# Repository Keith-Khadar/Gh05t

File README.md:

# Project Overview

This project aims to design and develop a wearable EEG headset with an integrated data acquisition system. Using OpenBCI Ultracortex Mark IV as a template, the headset is designed to map the electrodes according to the 10-20 system. We expand on this design by integrating our own 3D printed or button-snap electrodes for enhanced modularity. Additionally, we investigate various EEG data acquistion hardware options, varying in cost, precision, and usability, to enhance accessibility and modularity in EEG systems - ranging from off-the-shelf hardware to custom-designed PCBs and circuit designs. The hardware will communicate with a computer for analysis by a machine learning (ML) model to detect gestures or possible speech, with the possibility of integration into Virtual-Reality (VR) applications. Lastly, the system will feature a custom GUI, enabling users to visualize EEG data in real-time from the various custom hardware configurations we explore.

We provide various levels to users depending on cost, precision, and usability:

| Feature                     | High Performance Development Board[^1]    | Balanced Performance Board[^2]                | Low Cost EEG Filtering Circuit[^3]            |
| --------------------------- | ----------------------------------------- | --------------------------------------------- | --------------------------------------------- |
| **Number of Channels**      | 8\*                                       | 8\*                                           | 8                                             |
| **Resolution**              | 24-bit                                    | 24-bit                                        | 12-bit                                        |
| **Typical Sampling Rate**   | 250 Hz                                    | 250 Hz                                        | <33 Hz                                        |
| **ADC Chip**                | ADS1299-IPAG                              | ADS1299-IPAG                                  | Internal RPi Pico ADC                         |
| **Board**                   | EEG Development Board with ESP32-S3       | Custom PCB                                    | Custom breadboard/featherboard circuit        |
| **Microcontroller**         | XIAO ESP32-C6                             | DFRobot Firebeetle ESP32 32D                  | Raspberry Pi Pico W                           |
| **Connectivity**            | USB-C/Bluetooth/WiFi                      | Micro-USB/Bluetooth/WiFi                      | Micro-USB/WiFi                                |
| **Power Source**            | Battery/USB                               | Battery/USB                                   | Battery/USB                                   |
| **Battery Life**            | 8 hours                                   | -                                             | <1 hour                                       |
| **GUI Support**             | OpenBCI GUI                               | Custom GUI                                    | Custom GUI                                    |
| **Form Factor**             | Button Snap Electrodes w/ OpenBCI Headset | 3D printed Claw Electrodes w/ OpenBCI Headset | 3D printed Claw Electrodes w/ Custom Headband |
| **Communication Protocols** | SPI, ESPNOW, UART                         | SPI, BLE                                      | UDP WebSocket                                 |
| **Price**                   | ~$375                                     | ~$100                                         | ~$50                                          |

\* The ADS1299 has the capabilities to daisy chain, therefore expanding the channel number from 8 to 16 but it is not fully implemented on the custom PCB. Refer to the ADS1299 PCB folder for additional information.

[^1]: Refer to [High_Performance\README.md](https://github.com/Keith-Khadar/Gh05t/tree/main/High_Performance) for more information on the setup and specifics for the system.
[^2]: Refer to [Balanced_Performance\README.md](https://github.com/Keith-Khadar/Gh05t/tree/main/Balanced_Performance) for more information on the setup and specifics for the system.
[^3]: Refer to [Low_Cost\README.md](https://github.com/Keith-Khadar/Gh05t/tree/main/Low_Cost) for more information on the setup and specifics for the system.

## Completed Work/In Progress for Milestone Production Release

-   **Working Balanced Performance Pipeline (ADS1299 Breakout PCB)**: Eye blinks were detected successfully in the FFT and Time Series plots but was unable to receive consistent and robust results after each trial.
    -   Work in progress of doing trial and error to reproduce results.
-   **Housing Design for Balanced Performance Board (Breakout PCB)**: A CAD design of a housing unit for the ADS1299 Breakout PCB was completed.
-   **Receiver code optimization for the High Performance board**: The receiver code was optimized for better efficiency on the high-performance board by restructuring logic, minimizing redundant operations, and improving resource utilization.
-   **Optimizing Real Time Reading on the GUI**: Since eye blinks were successfully shown in the time series, the SDED, with the calibration of the delta and alpha variables, was able to successfully label with minimal latency the sample positions where the blinking occurred.
-   **EEG Game Application**: In order to expand the application of using the EEG data and detecting events like eye blinking, a VR and simple blinking game was created. A WebSocket host was created in the GUI and successfully broadcasts the SDED labels to any client to act as a controller for a game.
-   **Signal Preprocessing** : The EEG signal preprocessing pipeline is fully implemented, ensuring artifact removal, filtering, and independent component extraction before further processing. FastICA, InfoMax, NLMS and VSS-APA are implemented to extract information components from raw EEG signals in real-time.
-   **Event Detection/Prediction Model**: The EEG-based event detection pipeline and machine learning models have been developed to analyze real-time brain activity and infer motor function. NLMS, Batch-Wiener Filter and VSS-APA have been implemeted for predictions - Statistical Deviation Event Detection Model and Information Theoretic Learning Point Process Detection Models have been implemented for more sophisticed event flagging.

# Project Architecture

### <p align="center">**High Performance Development Board**[^1]</p>

| <div style="width:400px">Hardware Architecture & Wiring</div>  | Components  | Communication Protocols  |
| ----------------------- | ----------------------- | ----------------------- |
|  | - OpenBCI 3D Headset Design<br> - Depth-adjustable spring loaded 3D printed assembly with metal snap electrodes provides good signal strength for EEG signals <br> - EEG ESP Development Board with ESP32-S3 <br> - XIAO ESP32-C6<br> - Protective case for the development board<br> | - SPI communication between ADS1299 chip and ESP32-S3<br> - ESP-NOW WiFi data transmission between Development Board and ESP32-C6<br> - UART serialized data transmission through USB-C connection between ESP32-C6 and computer receiver <br> |

-   **Software**
    -   Once the ESP32-C6 captures the incoming EEG data from the ESP32-S3, the UART data is captured through a python script and written to a file. The captured EEG data in this file can be viewed using OpenBCI GUI. The EEG data in this file will be feed to the machine learning model to draw inferences after analysis of the data.
    -   A python script is employed to label and timestamp the 8-channel EEG blinking data. This script facilitates the real-time processing and organization of the data, ensuring that each blink event is accurately marked with its corresponding timestamp for subsequent analysis.
    -   An end-to-end high-performance EEG pipeline leverages an ESP32 EEG board and ESP32-C6 to wirelessly transmit 8-channel, ultra-low-noise data at 250 samples/sec via ESP-NOW, enabling real-time processing in Python and visualization through OpenBCI GUI or a custom interface.

### <p align="center">**Balanced Performance Board**[^2]</p>

| <div style="width:450px">Hardware Architecture & Wiring</div>  | Components  | Communication |
| ----------------------- | ----------------------- | ----------------------- |
|    | - OpenBCI 3D Headset Design<br> - 3D Printed Claw Electrodes<br> - Custom ADS1299 PCB<br> - DFRobot Firebeetle ESP32 32D <br> | - SPI communication between the ADS1299 PCB and Firebeetle ESP32 <br> - BLE data transmission between the Firebeetle ESP32 and computer receiver <br> |

-   **Software**
    -   Once the Firebeetle ESP32 is supplied power, the BLE server is turned on and ready to transmit data to any device that connects to the server. The **GH05T GUI** is used to connect to the BLE server and read incoming real-time data.

### <p align="center">**Low Cost Filtering Circuit**[^3]</p>

| <div style="width:500px">Hardware Architecture & Wiring</div>   | Components | Communication Protocols |
| ----------------------- | ----------------------- | ----------------------- |
|  | - Custom Filtering and Component Circuit on breadboard/featherboard <br> - Raspberry Pi Pico W <br> | - TCP WebSocket data transmission between Raspberry Pi Pico W and computer receiver |

-   **Software**
    -   Once the Raspberry Pi Pico W is supplied power,UDP WebSocket is opened and transmits data to any device that connects to the server. The **GH05T GUI** is used to connect to the WebSocket server and read incoming real-time data.

### <p align="center">**GH05T Graphic User Interface**[^4]</p>

| <div style="width:300px">Function and Feature Architecture</div> | Visuals/GUI  |
| ----------------| ---------------------- |
|  |  [PyQt](https://doc.qt.io/qtforpython-6/) & [Matplotlib](https://matplotlib.org/): Widget and EEG Data Visualization |

[^4]: Refer to [Gh05t GUI\README.md](https://github.com/Keith-Khadar/Gh05t/tree/main/Gh05t%20GUI) for more information on the setup and specifics on the GUI.

### <p align="center">**Signal Processing and Machine Learning**[^5]</p>

-   **EEG Signal Pre-processing**:

    -   Format:
        -   Input: Raw 4 channel electrode data
        -   Output: K-Independent Signals (Components)
    -   Processing Options:
        -   FastICA , NLMS: Fast Inference
        -   InfoMax or VSS-APA: Versatility & Robustness

-   **EEG Signal Machine Learning**:
    -   Format:
        -   Input: K-Independent Signals (Components)
        -   Output: User Defined Target Output
    -   Target:
        -   User Defined Target Desired Output, i.e. eye activity or motion.
    -   Model:
        -   Structure: Artifical Neural Network (Regressor)
        -   Pre-Training: PCA-Pretraining for optimal features
        -   Training: Network Tuning based on Target Data

[^5]: Refer to [Machine_Learning\README.md](https://github.com/Keith-Khadar/Gh05t/tree/main/Machine_Learning) for more information on the setup and specifics.

## Known Bugs

- The Balanced Performance Board ADS1299 completely stopped working after trying to fit the casing to the hardware. This was an unexpected issue that is not able to be understood. Possible issues that could have occurred for the chip to completely stop working is somehow the chip received a surge of power that could have damaged it. 

## Difficulties/Challenges

-   **3D Printing Fail**: Weak legs on 3D electrodes
    -   The initial model found and used for the electrodes has spindly legs. In combination with two snaps of the filament during printing, the legs were incredibly weak and many snapped during removal from the print bed.
    -   Fix: Load filament onto spool to eliminate snapping during print. Custom design electrodes with filleted legs to enhance their strength. Increase the number of walls when slicing model for printing.
    -   Above fix solved combined with printing on a higher quality printer and in a different orientation fixed the issues.
-   **Snap Plating**: Purchased snaps are covered in non-conductive coating
    -   Prevented soldering, but can be scrapped off with a knife.
    -   Reduces signal integritty of electrodes.
    -   Fix: Looking into alternative unplated snap connectors.
    -   Above fix solves the issue in initial testing. Will continue to monitor as further testing is conducted.
-   **Inaccurate EEG Data**: Data recorded during initial testing is inaccurate.
    -   The poor quality electrodes(see snap plating challenge & 3d printing fail) as well as the ADC optimized for Electromyography (EMG) data recording instead of the use case of Electroencephalography (EEG), resulted in poor quality data.
    -   Fix: Custom designed PCB breakout board for the ADS1299 which is designed for EEG data acquisition.
-   **GUI Real Time Data**: Optimizing the timing between data conversion from the ADS1299 to the GUI has introduced latency.
    -   Fix: Utilizing threading and precise timing between frame updating and loading.
-   **ADS1299 Electrode Setup**: Setting up the registers for specific BIAS, SRB1/2, and Electrode connections proved difficult with our system. This was causing reading alpha waves to be difficult.
    -   Fix: Using the SRB1, connected to the earlobe/mastoid, routed to all the negative parts of the electrode channels for reference. Using the BIAS, also connected to the earlobe/mastoid, routed to the postive electrode channels for signal derivation.

## License

## Contact

## Acknowledgements

We would like to extend our gratitude to OpenBCI for having open source repositories with headset designs, ADS1299 libraries, and user interface code. These repositories played a significant role in the success of the project!

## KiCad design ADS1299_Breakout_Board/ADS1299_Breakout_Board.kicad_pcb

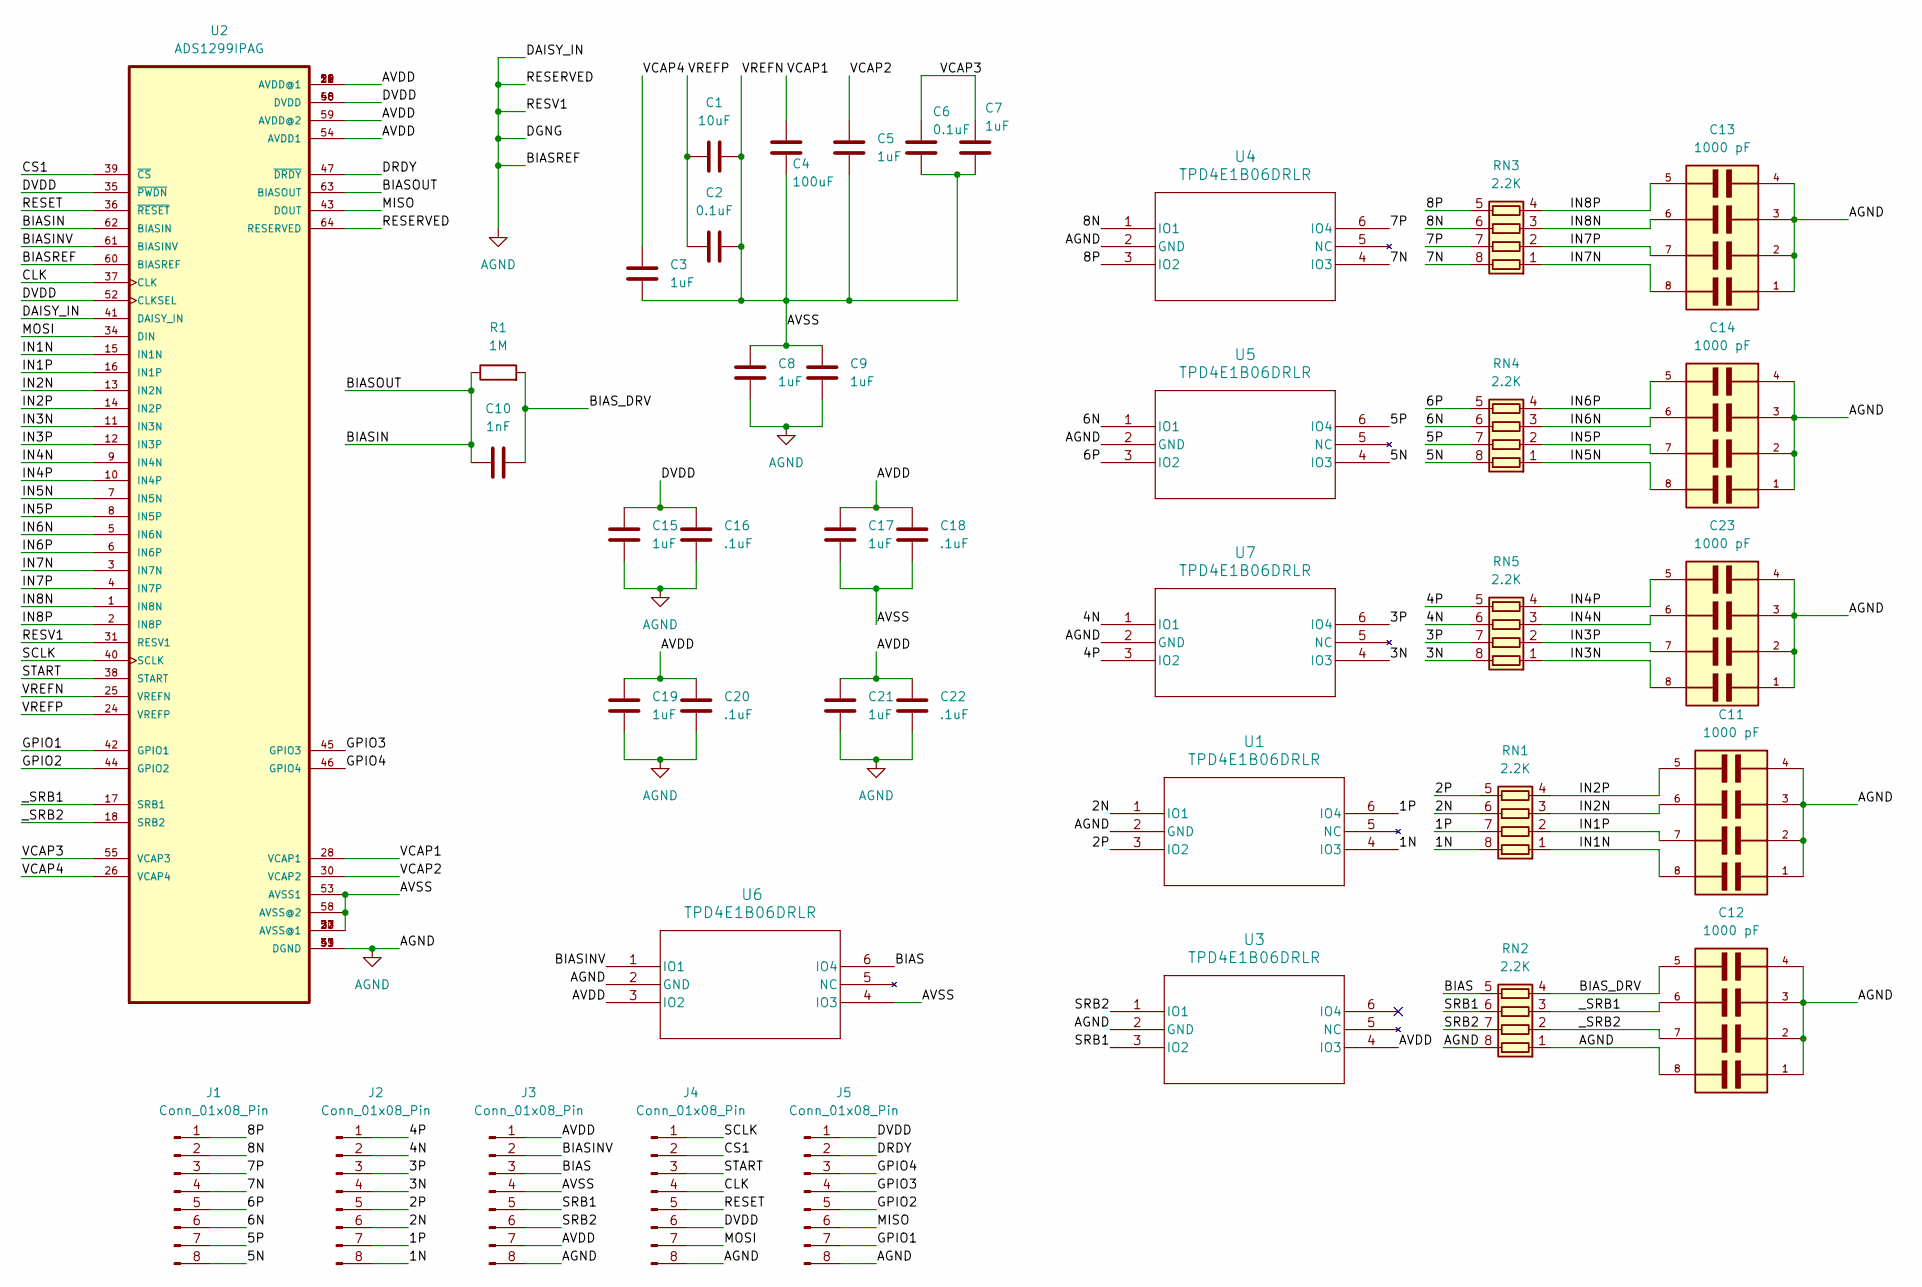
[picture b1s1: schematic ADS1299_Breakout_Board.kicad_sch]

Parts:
C1: 10uF; C_0805_2012Metric
C2, C6: 0.1uF; C_0805_2012Metric
C3, C5, C7, C8, C9, C15, C17, C19, C21: 1uF; C_0805_2012Metric
C4: 100uF; C_0805_2012Metric
C10: 1nF; C_0805_2012Metric
C11, C12, C13, C14, C23: 1000 pF; CAPCAF50P200X125X85-8; PARTREV Dec 2014
C16, C18, C20, C22: .1uF; C_0805_2012Metric
J1, J2, J3, J4, J5: Conn_01x08_Pin; PinHeader_1x08_P2.54mm_Vertical
R1: 1M; R_0805_2012Metric
RN1, RN2, RN3, RN4, RN5: 2.2K; R_Array_Concave_4x0603
U1, U3, U4, U5, U6, U7: TPD4E1B06DRLR; DRL6_TEX
U2: ADS1299IPAG; QFP50P1200X1200X120-64N

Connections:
/1N: J2.8, RN1.8 (R1.2), U1.4 (IO3)
/1P: J2.7, RN1.7 (R2.2), U1.6 (IO4)
/2N: J2.6, RN1.6 (R3.2), U1.1 (IO1)
/2P: J2.5, RN1.5 (R4.2), U1.3 (IO2)
/3N: J2.4, RN5.8 (R1.2), U7.4 (IO3)
/3P: J2.3, RN5.7 (R2.2), U7.6 (IO4)
/4N: J2.2, RN5.6 (R3.2), U7.1 (IO1)
/4P: J2.1, RN5.5 (R4.2), U7.3 (IO2)
/5N: J1.8, RN4.8 (R1.2), U5.4 (IO3)
/5P: J1.7, RN4.7 (R2.2), U5.6 (IO4)
/6N: J1.6, RN4.6 (R3.2), U5.1 (IO1)
/6P: J1.5, RN4.5 (R4.2), U5.3 (IO2)
/7N: J1.4, RN3.8 (R1.2), U4.4 (IO3)
/7P: J1.3, RN3.7 (R2.2), U4.6 (IO4)
/8N: J1.2, RN3.6 (R3.2), U4.1 (IO1)
/8P: J1.1, RN3.5 (R4.2), U4.3 (IO2)
/AVDD: C17.1, C18.1, C19.1, C20.1, C21.1, C22.1, J3.1, J3.7, U2.19 (AVDD@1), U2.21 (AVDD@1), U2.22 (AVDD@1), U2.54 (AVDD1), U2.56 (AVDD@1), U2.59 (AVDD@2), U3.4 (IO3), U6.3 (IO2)
/AVSS: C1.2, C2.2, C3.2, C4.2, C5.2, C6.1, C7.2, C8.1, C9.1, C17.2, C18.2, J3.4, U2.20 (AVSS@1), U2.23 (AVSS@1), U2.25 (VREFN), U2.32 (AVSS@1), U2.53 (AVSS1), U2.57 (AVSS@1), U2.58 (AVSS@2), U6.4 (IO3)
/BIAS: J3.3, RN2.5 (R4.2), U6.6 (IO4)
/BIASIN: C10.2, R1.1, U2.62 (BIASIN), U2.63 (BIASOUT)
/BIASINV: J3.2, U2.61 (BIASINV), U6.1 (IO1)
/BIAS_DRV: C10.1, C12.5, R1.2, RN2.4 (R4.1)
/CLK: J4.4, U2.37 (CLK)
/CS1: J4.2, U2.39 (~CS)
/DRDY: J5.2, U2.47 (~DRDY)
/DVDD: C15.1, C16.1, J4.6, J5.1, U2.35 (~PWDN), U2.48 (DVDD), U2.50 (DVDD), U2.52 (CLKSEL)
/GPIO1: J5.7, U2.42 (GPIO1)
/GPIO2: J5.5, U2.44 (GPIO2)
/GPIO3: J5.4, U2.45 (GPIO3)
/GPIO4: J5.3, U2.46 (GPIO4)
/IN1N: C11.8, RN1.1 (R1.1), U2.15 (IN1N)
/IN1P: C11.7, RN1.2 (R2.1), U2.16 (IN1P)
/IN2N: C11.6, RN1.3 (R3.1), U2.13 (IN2N)
/IN2P: C11.5, RN1.4 (R4.1), U2.14 (IN2P)
/IN3N: C23.8, RN5.1 (R1.1), U2.11 (IN3N)
/IN3P: C23.7, RN5.2 (R2.1), U2.12 (IN3P)
/IN4N: C23.6, RN5.3 (R3.1), U2.9 (IN4N)
/IN4P: C23.5, RN5.4 (R4.1), U2.10 (IN4P)
/IN5N: C14.8, RN4.1 (R1.1), U2.7 (IN5N)
/IN5P: C14.7, RN4.2 (R2.1), U2.8 (IN5P)
/IN6N: C14.6, RN4.3 (R3.1), U2.5 (IN6N)
/IN6P: C14.5, RN4.4 (R4.1), U2.6 (IN6P)
/IN7N: C13.8, RN3.1 (R1.1), U2.3 (IN7N)
/IN7P: C13.7, RN3.2 (R2.1), U2.4 (IN7P)
/IN8N: C13.6, RN3.3 (R3.1), U2.1 (IN8N)
/IN8P: C13.5, RN3.4 (R4.1), U2.2 (IN8P)
/MISO: J5.6, U2.43 (DOUT)
/MOSI: J4.7, U2.34 (DIN)
/RESET: J4.5, U2.36 (~RESET)
/SCLK: J4.1, U2.40 (SCLK)
/SRB1: J3.5, RN2.6 (R3.2), U3.3 (IO2)
/SRB2: J3.6, RN2.7 (R2.2), U3.1 (IO1)
/START: J4.3, U2.38 (START)
/VCAP1: C4.1, U2.28 (VCAP1)
/VCAP2: C5.1, U2.30 (VCAP2)
/VCAP3: C6.2, C7.1, U2.55 (VCAP3)
/VCAP4: C3.1, U2.26 (VCAP4)
/VREFP: C1.1, C2.1, U2.24 (VREFP)
/_SRB1: C12.6, RN2.3 (R3.1), U2.17 (SRB1)
/_SRB2: C12.7, RN2.2 (R2.1), U2.18 (SRB2)
AGND: C8.2, C9.2, C11.1, C11.2, C11.3, C11.4, C12.1, C12.2, C12.3, C12.4, C12.8, C13.1, C13.2, C13.3, C13.4, C14.1, C14.2, C14.3, C14.4, C15.2, C16.2, C19.2, C20.2, C21.2, C22.2, C23.1, C23.2, C23.3, C23.4, J3.8, J4.8, J5.8, RN2.1 (R1.1), RN2.8 (R1.2), U1.2 (GND), U2.31 (RESV1), U2.33 (DGND), U2.41 (DAISY_IN), U2.49 (DGND), U2.51 (DGND), U2.60 (BIASREF), U2.64 (RESERVED), U3.2 (GND), U4.2 (GND), U5.2 (GND), U6.2 (GND), U7.2 (GND)

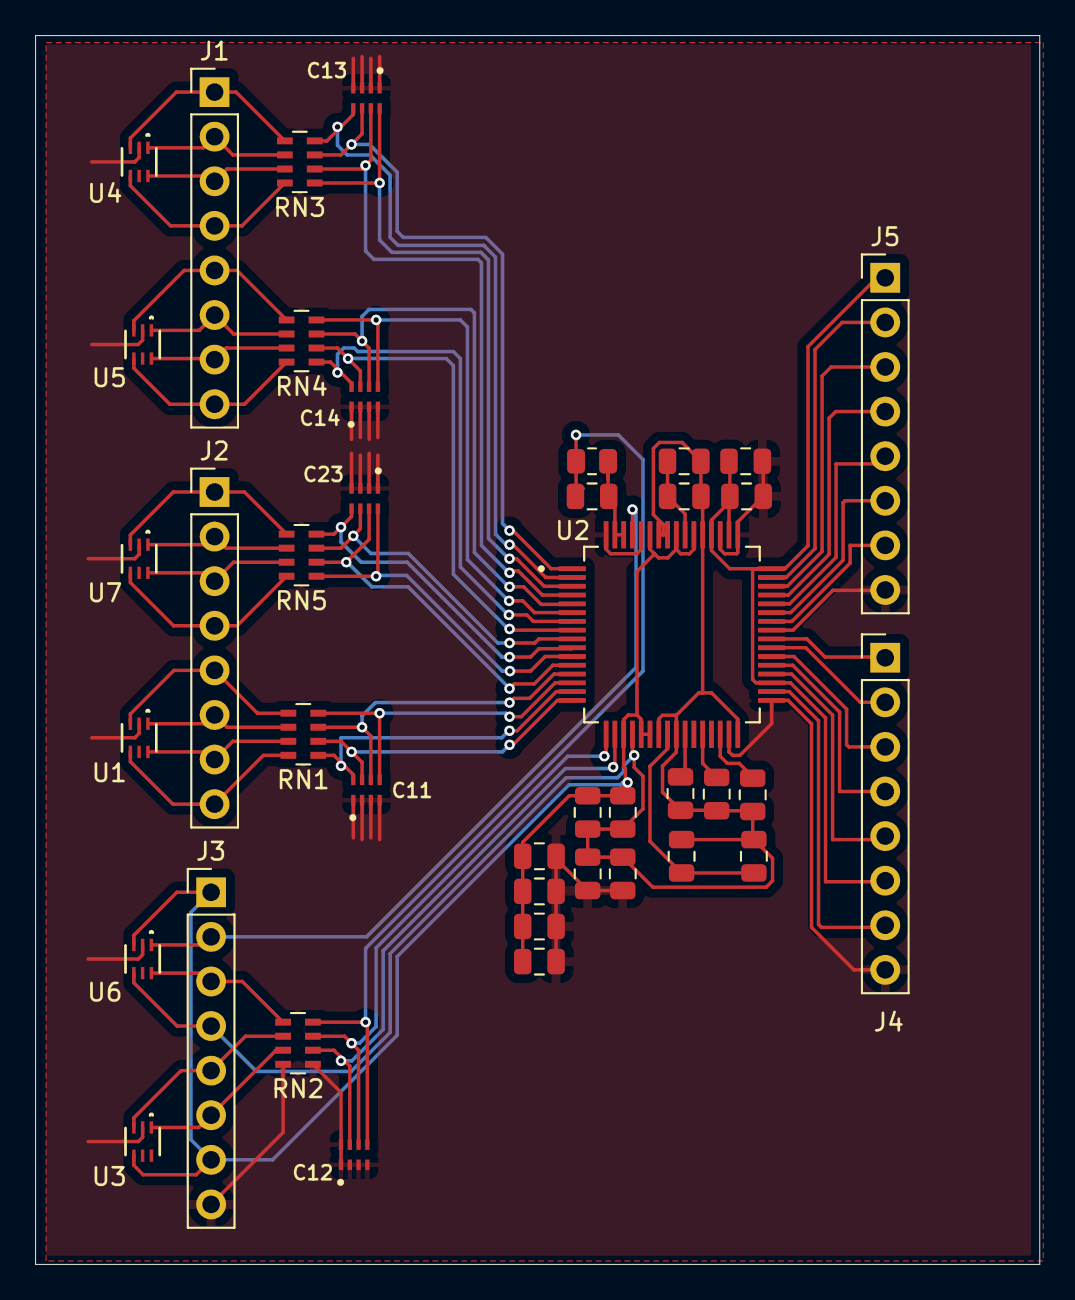
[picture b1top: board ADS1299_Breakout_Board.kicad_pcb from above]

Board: 2 copper layers, 57.2 x 70.0 mm, 41 parts (0 on the bottom side), 61 nets.

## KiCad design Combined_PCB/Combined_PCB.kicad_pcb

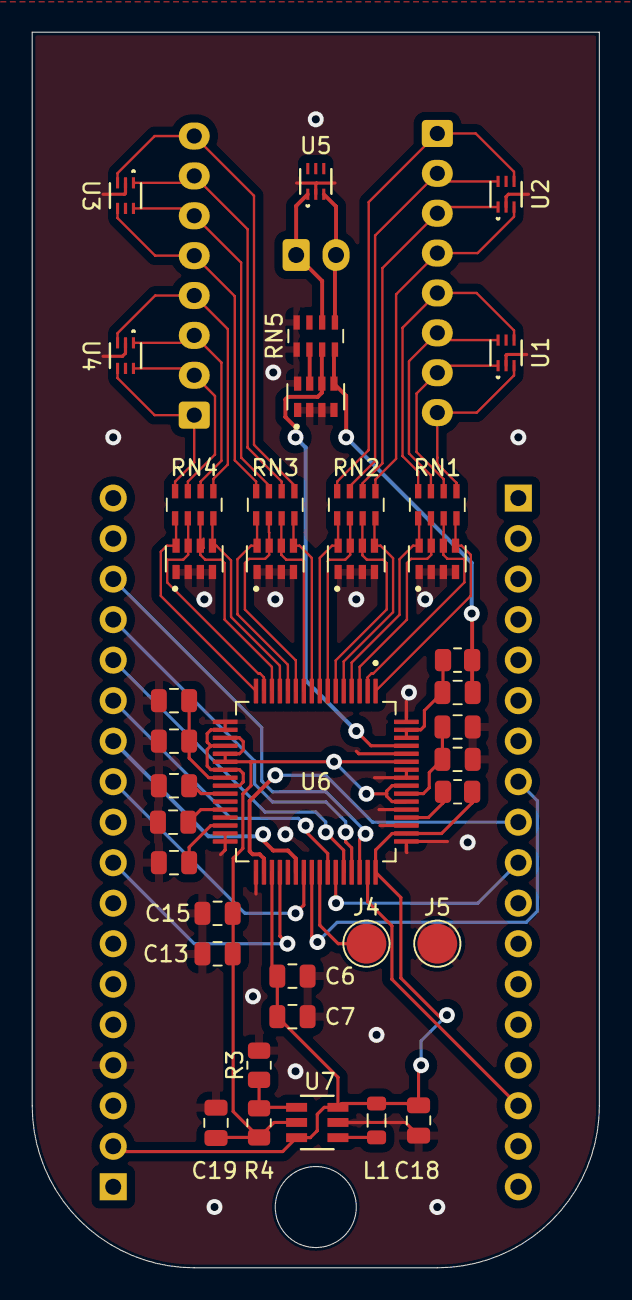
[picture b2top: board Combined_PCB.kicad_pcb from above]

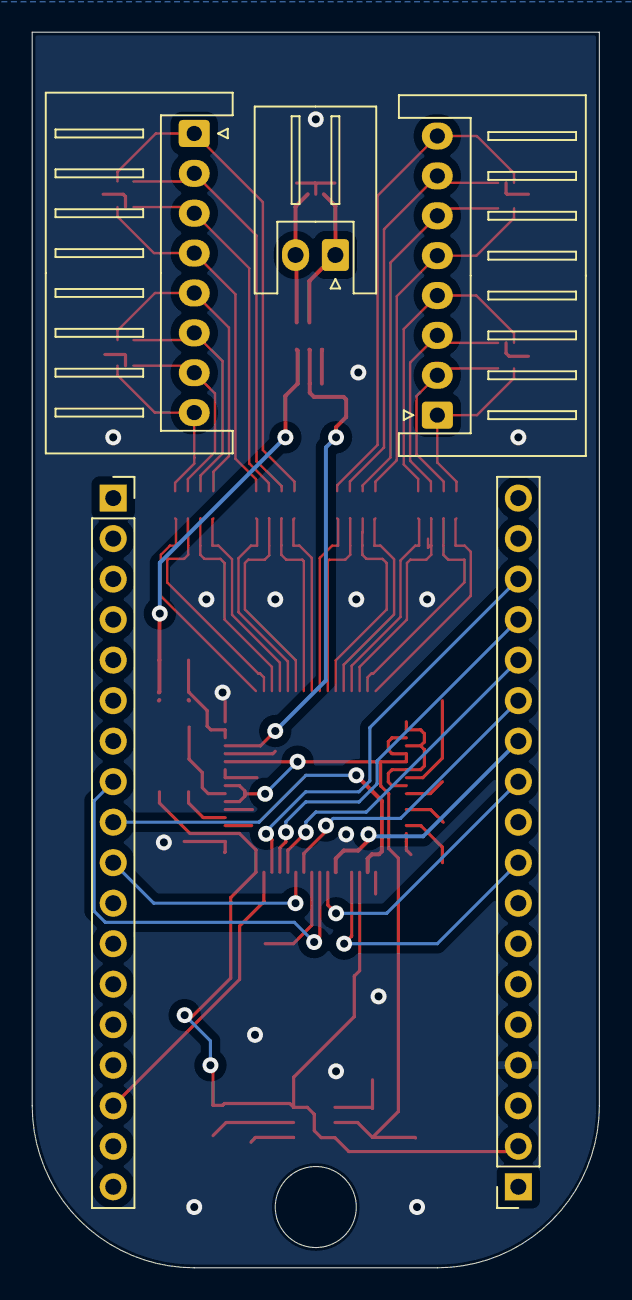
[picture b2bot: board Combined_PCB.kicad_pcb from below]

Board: 4 copper layers, 35.6 x 77.5 mm, 43 parts (5 on the bottom side), 61 nets.

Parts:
C1, C2, C3, C4, C5: 1000 pF; CAPCAV_W3A45C102KAT2A-8
C6, C12, C13, C16, C17: 1uF; C_0805_2012Metric
C7, C15: .1uF; C_0805_2012Metric
C8, C18, C19: 10uF; C_0805_2012Metric
C9, C14: 0.1uF; C_0805_2012Metric
C10: 100uF; C_0805_2012Metric
C11: 1nF; C_0805_2012Metric
J1, J3: Conn_01x08_Pin; JST_XH_S8B-XH-A_1x08_P2.50mm_Horizontal
J2: Conn_01x02_Pin; JST_XH_S2B-XH-A_1x02_P2.50mm_Horizontal
J4, J5: Conn_01x01_Pin; TestPoint_Pad_D2.5mm
J6, J7: Conn_01x18_Pin; PinSocket_1x18_P2.54mm_Vertical
L1: 4.7uH; L_0805_2012Metric
R1, R2: 1M; R_0805_2012Metric
R3: 309; R_0805_2012Metric
R4: 976; R_0805_2012Metric
RN1, RN2, RN3, RN4, RN5: 2.2K; R_Array_Concave_4x0603
U1, U2, U3, U4, U5: TPD4E1B06DRLR; DRL6_TEX
U6: ADS1299IPAG; QFP50P1200X1200X120-64N
U7: MCP1640BT-I/CHY; SOT-23-6_MC_MCH

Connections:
/ADS1299 & Microcontroller/3v3: C6.1, C7.1, C18.2, J6.2, L1.2, R2.2, U6.35 (~PWDN), U6.48 (DVDD), U6.50 (DVDD), U7.3 (EN), U7.6 (VIN)
/ADS1299 & Microcontroller/5v: C13.1, C15.1, C19.1, R4.2, U6.19 (AVDD@1), U6.21 (AVDD@1), U6.22 (AVDD@1), U6.54 (AVDD1), U6.56 (AVDD@1), U6.59 (AVDD@2), U7.5 (VOUT)
/ADS1299 & Microcontroller/BIASOUT: C11.2, R1.1, U6.62 (BIASIN), U6.63 (BIASOUT)
/ADS1299 & Microcontroller/CLK_SEL: R2.1, U6.52 (CLKSEL)
/ADS1299 & Microcontroller/CS: J6.11, U6.39 (~CS)
/ADS1299 & Microcontroller/DRDY: J7.16, U6.47 (~DRDY)
/ADS1299 & Microcontroller/GPIO1: J6.13, U6.42 (GPIO1)
/ADS1299 & Microcontroller/GPIO2: J6.14, U6.44 (GPIO2)
/ADS1299 & Microcontroller/GPIO3: J6.15, U6.45 (GPIO3)
/ADS1299 & Microcontroller/GPIO4: J6.16, U6.46 (GPIO4)
/ADS1299 & Microcontroller/MISO: J7.10, U6.43 (DOUT)
/ADS1299 & Microcontroller/MOSI: J7.9, U6.34 (DIN)
/ADS1299 & Microcontroller/RESET: J6.9, U6.36 (~RESET)
/ADS1299 & Microcontroller/SCLK: J7.8, U6.40 (SCLK)
/ADS1299 & Microcontroller/START: J6.12, U6.38 (START)
/ADS1299 & Microcontroller/VCAP1: C10.1, U6.28 (VCAP1)
/ADS1299 & Microcontroller/VCAP2: C12.1, U6.30 (VCAP2)
/ADS1299 & Microcontroller/VCAP3: C14.2, C16.1, U6.55 (VCAP3)
/ADS1299 & Microcontroller/VCAP4: C17.1, U6.26 (VCAP4)
/ADS1299 & Microcontroller/VREFP: C8.1, C9.1, U6.24 (VREFP)
/Inputs & Filtering/1N: J3.2, RN4.7 (R2.2), U4.6 (IO4)
/Inputs & Filtering/1P: J3.1, RN4.8 (R1.2), U4.4 (IO3)
/Inputs & Filtering/2N: J3.4, RN4.5 (R4.2), U4.3 (IO2)
/Inputs & Filtering/2P: J3.3, RN4.6 (R3.2), U4.1 (IO1)
/Inputs & Filtering/3N: J3.6, RN3.7 (R2.2), U3.6 (IO4)
/Inputs & Filtering/3P: J3.5, RN3.8 (R1.2), U3.4 (IO3)
/Inputs & Filtering/4N: J3.8, RN3.5 (R4.2), U3.3 (IO2)
/Inputs & Filtering/4P: J3.7, RN3.6 (R3.2), U3.1 (IO1)
/Inputs & Filtering/5N: J1.2, RN2.7 (R2.2), U2.6 (IO4)
/Inputs & Filtering/5P: J1.1, RN2.8 (R1.2), U2.4 (IO3)
/Inputs & Filtering/6N: J1.4, RN2.5 (R4.2), U2.3 (IO2)
/Inputs & Filtering/6P: J1.3, RN2.6 (R3.2), U2.1 (IO1)
/Inputs & Filtering/7N: J1.6, RN1.7 (R2.2), U1.6 (IO4)
/Inputs & Filtering/7P: J1.5, RN1.8 (R1.2), U1.4 (IO3)
/Inputs & Filtering/8N: J1.8, RN1.5 (R4.2), U1.3 (IO2)
/Inputs & Filtering/8P: J1.7, RN1.6 (R3.2), U1.1 (IO1)
/Inputs & Filtering/BIAS: J2.2, RN5.5 (R4.2), U5.3 (IO2)
/Inputs & Filtering/BIASINV: J2.1, RN5.6 (R3.2), U5.1 (IO1)
AGND: C1.1, C1.2, C1.3, C1.4, C2.1, C2.2, C2.3, C2.4, C3.1, C3.2, C3.3, C3.4, C4.1, C4.2, C4.3, C4.4, C5.1, C5.2, C5.3, C5.4, C5.8, C6.2, C7.2, C8.2, C9.2, C10.2, C12.2, C13.2, C14.1, C15.2, C16.2, C17.2, C18.1, C19.2, J5.1, J6.4, R3.2, RN5.1 (R1.1), RN5.8 (R1.2), U1.2 (GND), U2.2 (GND), U3.2 (GND), U4.2 (GND), U5.2 (GND), U6.20 (AVSS@1), U6.23 (AVSS@1), U6.25 (VREFN), U6.31 (RESV1), U6.32 (AVSS@1), U6.33 (DGND), U6.49 (DGND), U6.51 (DGND), U6.53 (AVSS1), U6.57 (AVSS@1), U6.58 (AVSS@2), U6.60 (BIASREF), U6.64 (RESERVED), U7.2 (GND)
DAISY_IN: J4.1, U6.41 (DAISY_IN)
IN1N: C4.7, RN4.2 (R2.1), U6.15 (IN1N)
IN1P: C4.8, RN4.1 (R1.1), U6.16 (IN1P)
IN2N: C4.5, RN4.4 (R4.1), U6.13 (IN2N)
IN2P: C4.6, RN4.3 (R3.1), U6.14 (IN2P)
IN3N: C3.7, RN3.2 (R2.1), U6.11 (IN3N)
IN3P: C3.8, RN3.1 (R1.1), U6.12 (IN3P)
IN4N: C3.5, RN3.4 (R4.1), U6.9 (IN4N)
IN4P: C3.6, RN3.3 (R3.1), U6.10 (IN4P)
IN5N: C2.7, RN2.2 (R2.1), U6.7 (IN5N)
IN5P: C2.8, RN2.1 (R1.1), U6.8 (IN5P)
IN6N: C2.5, RN2.4 (R4.1), U6.5 (IN6N)
IN6P: C2.6, RN2.3 (R3.1), U6.6 (IN6P)
IN7N: C1.7, RN1.2 (R2.1), U6.3 (IN7N)
IN7P: C1.8, RN1.1 (R1.1), U6.4 (IN7P)
IN8N: C1.5, RN1.4 (R4.1), U6.1 (IN8N)
IN8P: C1.6, RN1.3 (R3.1), U6.2 (IN8P)
INBIAS: C5.5, C11.1, R1.2, RN5.4 (R4.1)
INBIASINV: C5.6, RN5.3 (R3.1), U6.61 (BIASINV)
unnamed: C5.7, RN5.2 (R2.1)
unnamed: L1.1, U7.1 (SW)
unnamed: R3.1, R4.1, U7.4 (VFB)

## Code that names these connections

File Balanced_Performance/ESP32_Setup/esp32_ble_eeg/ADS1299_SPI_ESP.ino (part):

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  // MISO [DOUT] = GPIO 19
  // MOSI [DIN] = GPIO 23
  // CS = GPIO 13 // chip select pin
  // DRDY = GPIO 16 // data ready pin
  // RST = GPIO 2

  // VCC supplies 5V/AVDD while plugged via usb
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  // MISO [DOUT] = GPIO 20 or D9
  // MOSI [DIN] = GPIO 18 or D10
  // CS = GPIO 21 or D3 // chip select pin
  // DRDY = GPIO 1 or D1 // data ready pin
  // RST = GPIO 2 or D2

  // VCC supplies 5V/AVDD while plugged via usb
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  // MISO [DOUT] = GPIO 8 or D9
  // MOSI [DIN] = GPIO 9 or D10
  // CS = GPIO 44 or D7 // chip select pin
  // DRDY = GPIO 3 or D2 // data ready pin
  // RST = GPIO 2 or D1

  // VCC supplies 5V/AVDD while plugged via usb
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
void setup() {
  // --- FIREBEETLE ESP32 Dev ADS Configurations ---
  // ADS.initialize(16,2,5,2,0);          // (DRDY pin, RST pin, CS pin, SCK frequency in MHz, isDaisy bool);
  ADS.initialize(16, 2, 13, 1.5, 0);      // (DRDY, RST, CS, 1.5MHz)
  // --- ESP32 S3 XIAO SEEED ADS Configurations ---
  // ADS.initialize(3,2,44,2,0);
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  delay(1000);

  // Digital Inputs/Outputs Setup for FIREBEETLE
	pinMode(25, INPUT); // GPIO4
  pinMode(26, INPUT); // GPIO3
  pinMode(27, INPUT); // GPIO2
  pinMode(9, INPUT); // GPIO1
  pinMode(10, OUTPUT); // START

  // SETUP DEVICE (Datasheet pg. 62)
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
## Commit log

2024-10-03 Update README.md
    Add design draft link
2024-10-03 Update README.md
    edit link
2024-10-25 pre-alpha arduino
2024-10-25 Update README.md
    Template for readme
2024-10-25 Create gui.py
    Simple gui layout
2024-10-25 Rename Expected Arduino IDE output.png to Expected_Arduino_IDE_output.png
2024-10-25 Rename nRFConnect output.png to nRFConnect_output.png
2024-10-25 Rename nRFConnect_output.png to nRF_Connect_output.png
2024-10-26 Created Schematic for ADS1299 Breakout Board
2024-10-26 Basic CAD model
2024-10-26 Add files via upload
    Adding some setup files.
2024-11-12 Fixed some of the label names and started work on pcb
2024-11-12 didnt close kicad when last pushed
2024-11-14 Finished up traces
2024-11-15 Created gerber files and added component libraries
2024-11-15 Test
2024-11-15 Linked libraries to project
2024-11-15 Linked Footprint libraries
2024-11-15 Added 3d model to pcblayout
2024-11-19 Electrode Model + Components List
2024-11-19 Update PCB Schematic
2024-11-21 Updated code for ESP32C6 BLE connection with laptop
2024-11-22 Create temp
2024-11-22 Motion Estimation Files
2024-11-22 Adding Config Files (for ease)
2024-11-23 3D Pose Demo
2024-11-23 Update README.md
    Added demo video
2024-11-26 Filler files, not complete
2024-12-01 Added JupyterNotebook
2024-12-02 update gui
2024-12-02 Update code
2024-12-02 Update BLE
2024-12-03 update Waveform for BLE
2024-12-03 update BLE ino
2024-12-07 Update README.md
    Difficulties updated
2025-01-31 Update eeg headset
2025-02-01 new GUI framework
2025-02-06 Post-alpha build upload
2025-02-12 new additions
    added ADS1299 library to esp32 folder and gui can connect with ble to esp32
2025-02-13 More Electrode work, Start of Muxed PCB
2025-02-21 Adding unit tests and updated changes
2025-02-21 esp32 sketches with ads1299 library
2025-02-25 beta update
2025-02-25 Delete pose-recognition directory
    bye bye rtmpose
2025-02-25 Delete signal-preprocessing/ica_tools.py
    git outa here
2025-02-25 Delete signal-preprocessing/ica_testing.ipynb
    git outta here
2025-02-25 added rpi firmware to run low cost
2025-02-25 Add files via upload
    clarity update to document
2025-02-25 Create README.md for low cost
2025-02-25 repo organization
2025-02-25 Update README.md
    Added some usage description
2025-02-25 Update README.md
    updated ML stuffs
2025-02-25 Update README.md
    fixed technicalities
2025-03-04 debugging
2025-03-04 SDED Update
2025-03-05 C file including algorithm to apply.
2025-03-05 updated sded ipynb
2025-03-05 Included 2 SDED Methods, both inexpensive
2025-03-06 Updated ML Models
2025-03-06 Final Touches
2025-03-10 Archived in favor of combined pcb
2025-03-10 Final combined ppcb
2025-03-13 Semi-finalized PCB Layout final
2025-03-13 Schematic and footprints complete
2025-03-15 ADS1299 final pcb layout done (hopefully)
2025-03-18 Add CS
2025-03-18 Update with credit link
2025-03-24 update signal processing and labeling
2025-03-25 Final PCB Render Done
2025-03-28 Preliminary housing CAD
2025-03-28 update plots and labeling
2025-03-28 Event-Detection Adjusted Architecture for APA
2025-03-29 Update low cost file
2025-03-29 Reorganized Balanced Performance
2025-03-29 moved images around
2025-03-29 added pcb images
2025-03-29 Closed Kicad
2025-03-29 organizing folders
2025-03-29 More folder organization
2025-03-29 More folder stuff
2025-03-29 Final folder stuff
2025-04-01 Update ESP32
2025-04-02 V2 Housing
2025-04-03 Fix sample timing
2025-04-10 Add images of breakout board
2025-04-10 Update the balanced performance readme
2025-04-10 Update README links
2025-04-14 Created CAD for breakout board housing
2025-04-15 Update completed list for PR
2025-04-15 added simple unity game as example
2025-04-15 Update for Low Cost Eye Blinks
2025-04-15 added dont blink a vr game
2025-04-15 added ip input text box to blinky bird
2025-04-17 Update adaptive threshold
2025-04-22 Update with NLMS and SDED Adaptive Training
